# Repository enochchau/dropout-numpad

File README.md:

# Dropout 

(mechanical numpad w/ roatry encoder)

## Firmware
Dropout uses [QMK](https://github.com/qmk/qmk_firmware).
For now you'll have to use my fork of QMK under [the dropout-numpad branch](https://github.com/ec965/qmk_firmware/tree/dropout-numpad/keyboards/dropout).
If you know what you're doing, you can also copy the firmware files from this repository into your local QMK repository and compile it that way.

## Parts

### Case Parts
Amount | Part | Dimensions
--- | --- | ---
5 | M2 F-F standoffs | minimum: 13mm (mini usb) or 11mm (micro-usb)
10 | M2 screws | 5mm
4 | rubber bumpon feet

Sandwhich! case (parts in this order from top down)

1. Plate
2. PCB
3. Base

### PCB Components
Amount | Part | Package
--- | --- | ---
18 | diodes (1n4148 recommended) | SOD-123 (SMD) or DO-35 (THT)
1 | resistor (333 Ohms) | 0805
2 | capacitors (10nF) | 0805
1 | led | 1.8mm
1 | rotary encoder | EC-11
1 | push button | SPST PTS810
1 | pro-micro | usb-mini or usb-micro
16 | mx-switches | 
2 | 2U stabilizers | 

#### Notes
* Encoder can be swapped for a 1u switch.
  - If opting for the 1u switch, capacitors are not needed.
* If using encoder, capacitors can be omitted but resulting encoder signal will not be as smooth.
* Resistor can be omitted if num-lock led is not used.

## Build Guide

* The bottom of the PCB is the side without the stencil art of the person.
* The top of the PCB is the side with the stencil art person on it.

1. Start on the bottom of the PCB. Solder on all the diodes. Make sure that the diodes are in the correct direction. The diagram below should match up to the the symbol on the schematic and the physical diodes.

2. Solder on capacitors C1 and C2. These are located near the rotary encoder.

3. Solder on the resistor R1. It is near the num lock key. This resistor is to limit the current going to the num-lock led.

4. Solder on the SPST reset switch.

5. Solder on the Pro Micro header pins with the short side down. DO NOT solder on the Pro Micro.

6. Solder on the rotary encoder.

7. Flip the board over to the top side. You should now see the stencil art of the the person. Put two 2U stablizers on the board for the Zero and Enter keys.

    1. If you are using Kailh Box switches, solder on the num-lock LED before putting the switch on the board.
    2. If you are using regular Cherry, Gateron, etc. you can wait to solder the num-lock LED after all the switches are soldered on.

The polarity of the led is shown below.

8. Put the switches on the plate. Line up the plate with the pcb and push the two parts together. There may be some friction but as long as none of the switch pins get bent it is okay.

9. Flip the PCB over to the bottom side. As you solder on the switches, apply some pressure to push the plate into the PCB to ensure that the switches are flush with the PCB.

10. Tape the Pro Micro onto the header pins. 
Clip the long header pins to be flush with the holes on the Pro Micro.
Then, solder the Pro Micro to the header pins.

11. Put the standoffs through the holes on the top of the plate and screw them in.

12. Get the bottom plate and screw the other end of the standoffs into the bottom plate. The standoffs should go through the holes in the PCB.

13. Place rubber feet onto the bottom of the numpad.

## PCBs

* rev 0.5

* rev 0.1

## License

Hardware designs are under the MIT license. QMK is under the GPL v2 license therefore, the firmware is also under the GPLv2 license.

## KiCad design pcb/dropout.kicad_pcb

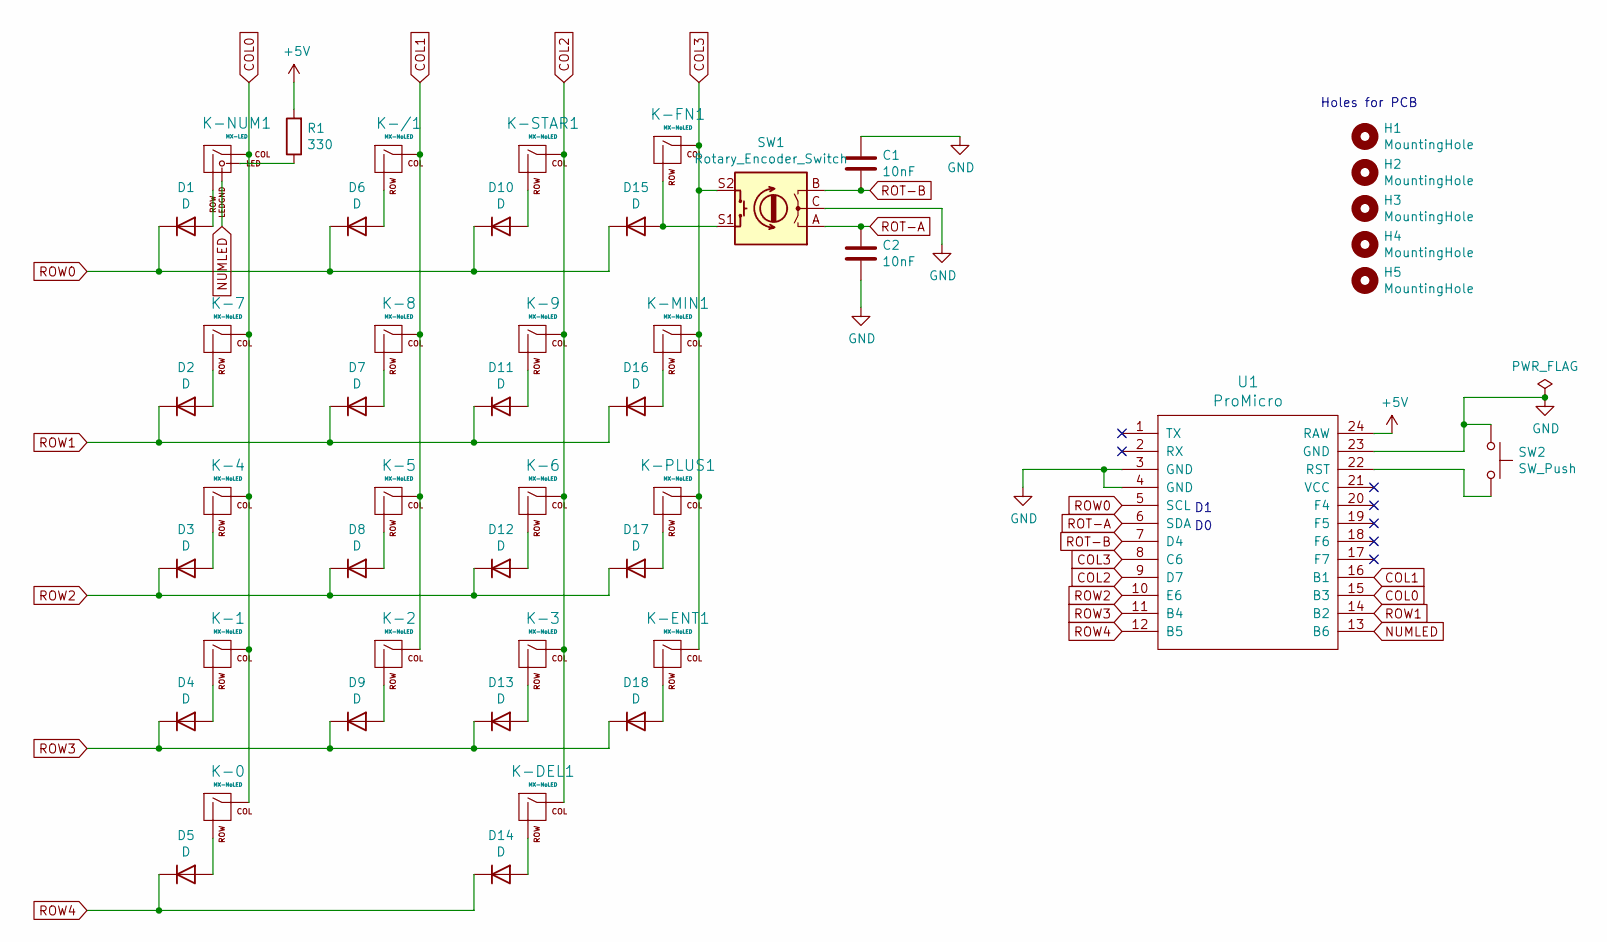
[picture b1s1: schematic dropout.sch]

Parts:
C1, C2: 10nF; C_0805_2012Metric_Pad1.15x1.40mm_HandSolder
D1, D2, D3, D4, D5, D6, D7, D8, D9, D10, D11, D12, D13, D14, D15, D16, D17, D18: D; Diode_TH_SOD123
H1, H2, H3, H4, H5: MountingHole; MountingHole_3.7mm
K-0: MX-NoLED; MXOnly-2U-ReversedStabilizers-NoLED
K-1, K-2, K-3, K-4, K-5, K-6, K-7, K-8, K-9: MX-NoLED; MXOnly-1U-NoLED
K-/1: MX-NoLED; MXOnly-1U-NoLED
K-DEL1: MX-NoLED; MXOnly-1U-NoLED
K-ENT1: MX-NoLED; MXOnly-2U-ReversedStabilizers-NoLED
K-FN1: MX-NoLED; MXOnly-1U-NoLED
K-MIN1: MX-NoLED; MXOnly-1U-NoLED
K-NUM1: MX-LED; MXOnly-1U
K-PLUS1: MX-NoLED; MXOnly-1U-NoLED
K-STAR1: MX-NoLED; MXOnly-1U-NoLED
R1: 330; R_0805_2012Metric_Pad1.15x1.40mm_HandSolder
SW1: Rotary_Encoder_Switch; RotaryEncoder_Alps_EC11E-Switch_Vertical_H20mm
SW2: SW_Push; SW_SPST_PTS810
U1: ProMicro; ProMico_mini&micro

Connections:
+5V: R1.2, U1.24 (RAW)
COL0: K-0.1 (COL), K-1.1 (COL), K-4.1 (COL), K-7.1 (COL), K-NUM1.1 (COL), U1.15 (B3)
COL1: K-2.1 (COL), K-5.1 (COL), K-8.1 (COL), K-/1.1 (COL), U1.16 (B1)
COL2: K-3.1 (COL), K-6.1 (COL), K-9.1 (COL), K-DEL1.1 (COL), K-STAR1.1 (COL), U1.9 (D7)
COL3: K-ENT1.1 (COL), K-FN1.1 (COL), K-MIN1.1 (COL), K-PLUS1.1 (COL), SW1.S2, U1.8 (C6)
GND: C1.1, C2.2, SW1.C, SW2.1, U1.3 (GND), U1.4 (GND), U1.23 (GND)
NUMLED: K-NUM1.4 (LEDGND), U1.13 (B6)
unnamed: D1.2 (A), K-NUM1.2 (ROW)
unnamed: D2.2 (A), K-7.2 (ROW)
unnamed: D3.2 (A), K-4.2 (ROW)
unnamed: D4.2 (A), K-1.2 (ROW)
unnamed: D5.2 (A), K-0.2 (ROW)
unnamed: D6.2 (A), K-/1.2 (ROW)
unnamed: D7.2 (A), K-8.2 (ROW)
unnamed: D8.2 (A), K-5.2 (ROW)
unnamed: D9.2 (A), K-2.2 (ROW)
unnamed: D10.2 (A), K-STAR1.2 (ROW)
unnamed: D11.2 (A), K-9.2 (ROW)
unnamed: D12.2 (A), K-6.2 (ROW)
unnamed: D13.2 (A), K-3.2 (ROW)
unnamed: D14.2 (A), K-DEL1.2 (ROW)
unnamed: D15.2 (A), K-FN1.2 (ROW), SW1.S1
unnamed: D16.2 (A), K-MIN1.2 (ROW)
unnamed: D17.2 (A), K-PLUS1.2 (ROW)
unnamed: D18.2 (A), K-ENT1.2 (ROW)
unnamed: K-NUM1.3 (LED), R1.1
unnamed: SW2.2, U1.22 (RST)
ROT-A: C2.1, SW1.A, U1.6 (SDA)
ROT-B: C1.2, SW1.B, U1.7 (D4)
ROW0: D1.1 (K), D6.1 (K), D10.1 (K), D15.1 (K), U1.5 (SCL)
ROW1: D2.1 (K), D7.1 (K), D11.1 (K), D16.1 (K), U1.14 (B2)
ROW2: D3.1 (K), D8.1 (K), D12.1 (K), D17.1 (K), U1.10 (E6)
ROW3: D4.1 (K), D9.1 (K), D13.1 (K), D18.1 (K), U1.11 (B4)
ROW4: D5.1 (K), D14.1 (K), U1.12 (B5)

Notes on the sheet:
Holes for PCB

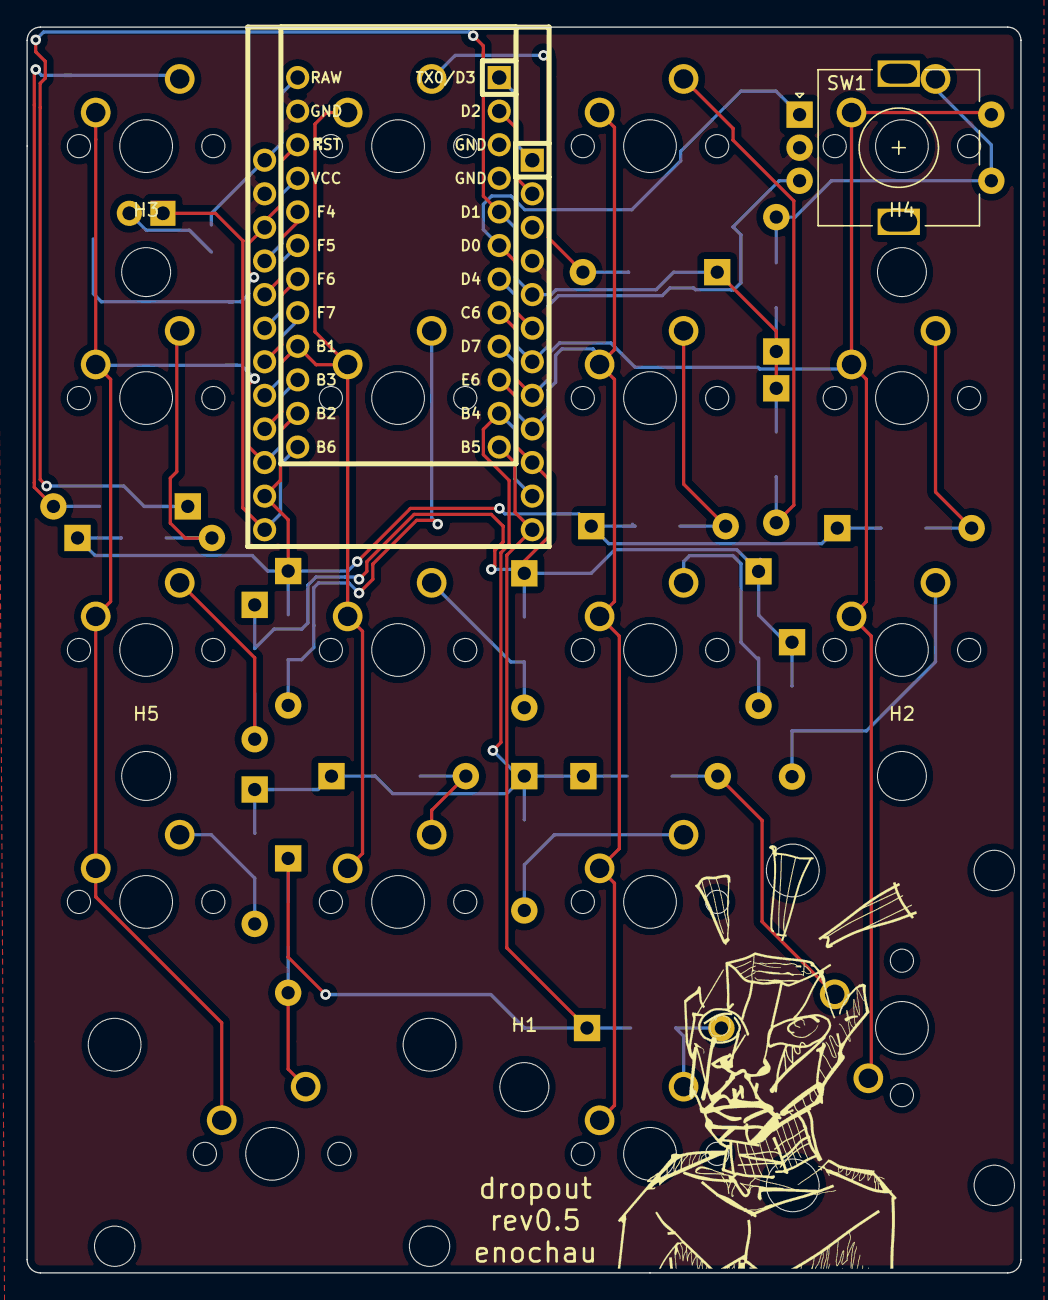
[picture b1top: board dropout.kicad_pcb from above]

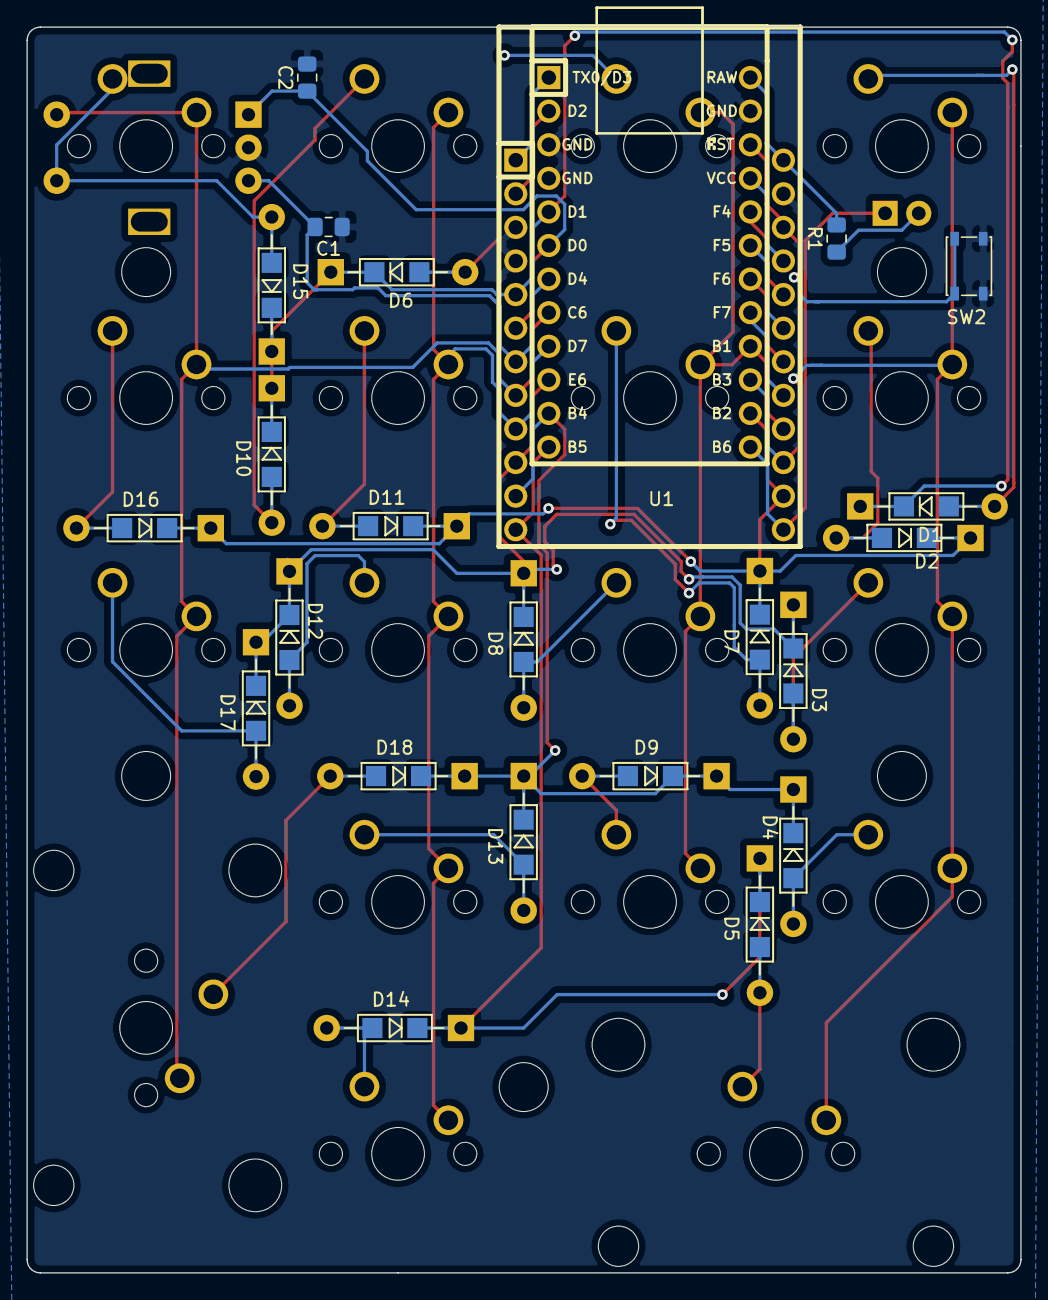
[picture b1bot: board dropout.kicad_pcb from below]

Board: 2 copper layers, 75.1 x 94.2 mm, 47 parts (23 on the bottom side), 34 nets.

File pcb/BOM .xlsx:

Reference | Quantity | Value | Footprint | Datasheet | Notes
D1 D2 D3 D4 D5 D6 D7 D8 D9 D10 D11 D12 D13 D14 D15 D16 D17 D18 | 18 | D | Diode_SMD:D_SOD-123 | ~
H1 H2 H3 H4 H5 | 5 | MountingHole | MountingHole:MountingHole_2.2mm_M2_Pad | ~ | screws and poles (8mm)
K-/1 K-STAR1 K-MIN1 K-PLUS1 K-1 K-DEL1 K-2 K-3 K-4 K-5 K-6 K-7 K-8 K-9 | 14 | MX-NoLED | MX_Only:MXOnly-1U-NoLED | Kailh Box Whites
K-0 K-ENT1 | 2 | MX-NoLED | MX_Only:MXOnly-2U-NoLED |  | 2u stabs
K-NUM1 | 1 | MX-LED | MX_Only:MXOnly-1U
R1 | 1 | 333 | Resistor_SMD:R_0805_2012Metric_Pad1.15x1.40mm_HandSolder | ~
SW1 | 1 | Rotary_Encoder_Switch | Rotary_Encoder:RotaryEncoder_Alps_EC11E-Switch_Vertical_H20mm | ~ | knob and encoder
SW2 | 1 | SW_Push | Button_Switch_SMD:SW_SPST_PTS810 | ~
U1 | 1 | ProMicro | promicro:ProMicro |  | mini usb, 39.5mmx23mm
PCB
C1 C2 | 2 | 10nF | 805

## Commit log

2020-12-04 init
2020-12-04 cleanup
2020-12-04 micro usb promicro
2020-12-04 remove bom w/ purchase links
2020-12-04 remove purchase link BOM
2020-12-04 add caps for encoder
2020-12-04 remove temp files
2020-12-04 firmware
2020-12-04 license
2020-12-04 move screws away from stabs
2020-12-07 3 piece panelization
2020-12-08 adding copper plated mounting holes
2020-12-12 rev 0.4
2020-12-12 generate gerbers for rev0.4
2020-12-12 labels for orientation of pro-micro
2020-12-12 qmk backlight numlock
2020-12-12 update readme with firmware
2020-12-12 rename cleanup
2020-12-12 update gerbers
2020-12-13 alt-layout, replace encoder w/ switch
2020-12-13 5v -> led -> pin (numlock led)
2020-12-13 i2c trrs connectors
2020-12-13 update readme picture
2020-12-13 replace i2c trrs with header pins
2020-12-28 working firmware
2020-12-28 Changing to MIT license
2020-12-28 updating to rev0.5
    updating to rev0.5
2020-12-28 fixing readme
2020-12-29 updating gerbers
2020-12-29 updating readme
2020-12-29 moving diodes to stop interference with stabilizer
2020-12-29 flipping orientation of promicro for better clearance, now uses same pinout as rev0.1
2020-12-30 adding graphics to pcb, some cleanup
2020-12-30 updating firmware
2020-12-30 updating spacer measurements
2020-12-30 flipped orientation of stab outline to match pcb
2020-12-30 breaking up panelization for production
2021-01-12 updating pics for rev0.5 pcb
2021-03-19 adding build guide
2021-03-19 minor revisions
2021-05-02 updating build guide
